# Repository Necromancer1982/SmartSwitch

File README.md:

# SmartSwitch
## Flush-mounted Module to control shutters / realize an intermediate switch with ESP8266

**Version History**

- SmartSwitch V1.2  04/2018   1st official public Version
- SmartSwitch V1.3  05/2018   ADD: Additional Fuse (F2, 4A) for consumer current
- **Software now avaliable for ArduinoIDE (including OTA)**

**Vision**

During the construction of our new house, we’ve decided to install motorized roller shutters. To control them, we first used only standard shutter-push-buttons, right beside the correspondent window. As second step a *smart solution* should be established.

Inspired by Leo-Andres Hofmann’s “230V I/O Modul für ESP8266” ([LUANI](https://luani.de/projekte/esp8266-hvio/)), I’ve decided to develop my own module to sense the shutter-push-buttons and control the motorization.
By its dimensions, the module perfectly fits into a standard round In-Wall-Pattress (inner diameter: 60mm). If its a so called "deep" pattress, the shutter-push-buttons can also be installed on top of the module and there is enough space left for wires and terminals.

Basis of the module is a ESP-12F, an integrated WLAN-Module which controls two changeover relays to move the shutters. 

The operation of the module can either be controlled by the already existing push-buttons, or via MQTT-Messages by WLAN, central controlled via [OpenHab2](https://docs.openhab.org/index.html), running on my Raspberry Pi Zero W. Therefore, a movement of the shutters regarding time or special events, for example time of dusk and down ([Astro Bindings](https://docs.openhab.org/addons/bindings/astro/readme.html)) can be realized. Also an automatized shadowing regarding sun position, global radiation and inside / outside temperature will be possible.

**Hardware**

Beside the WLAN-Module and the relays (contact rating 1500VA, 6A/250V), a power supply consisting of a AC/DC-Converter HI-Link HLK-PM01 (5V/600mA) to serve the relays and a voltage regulator TS1117 (LowDrop 3V) to serve the remaining circuit, a 2-chanel power sense circuit to detect 230V levels for the controller and interfaces like UART, I²C and analog/digital IO are included on the board. A push button for hardware reset is also implemented on bottom side of the PCB.

Three soldering jumpers give the opportunity to decide if the relays should act as an intermediate switch to implement the module in an already existing light-installation or to act as a roller-shutter-controlling device. Therefore, the first relay powers the motor during the second relay controls moving direction. Via a fourth soldering Jumper it is possible to supply mains voltage to the relays, so for roller shutter function, there is no need to connect phase two times, for supplying the module and supplying the motor. 

The power supply of the module is secured by a SMD-Fuse (500mA) and a varistor (275V) against overload.

**Software**

In addition to the firmware ([NodeMCU](https://nodemcu.readthedocs.io/en/master/)) there are mainly four LUA-Scripts on the Module.

The Init-File tries to connect to the access point whose SSID and password is stored at the ESP. If the connection couldn’t be established, the ESP himself opens an access point and starts an end user setup to give the user the possibility to enter SSID and password of an already existing access point (Router).

If the connection is established, two more software modules will be started. The MQTT-Module starts to configure the implemented MQTT-Client, opens a connection to the MQTT-Broker which is defined (IP, Port) in the MQTT.ini file and provides several procedures for MQTT communication. The INI-Handling-Module provides two more procedures for easy INI-File access by using “Key” and “Value” data.

Finally, the main program will be started.

:+1: _UPDATE_

Now I'd also written a new software for ArduinoIDE.
The main advantage of this new sketch is the possibility of updating the software via OTA (Over the Air update via WiFi).
After flashing the sketch via serial adapter for the first time, the module can be found and flashed via ArduinoIDE OTA-Functionality.

Additionally there are a few smaller upgrades and BugFixes implemented in the new software.

The functionality of the Arduino-Software is mostly the same as the LUA-Skript.
The module tries to connect to the last stored access point. If no connection could be established the module starts its implemented enduser setup. SSID and password of the AP and also the site of usage and MQTT-borker IP can be configured. After this initialisation the module starts its normal operation and can be either controlled via the already existing push buttons or MQTT-Commands.

**Function**

During normal operation, the main program offers the opportunity to control the module via the shutter-push-buttons by using both of the power sense inputs. (Only LUA-Skript: If both buttons were pushed synchronously the module changes to teaching mode.) Via MQTT-Command "TEACH", the module changes to teaching mode. Because of the fact that simple shutter motors neither feedback their position nor the state of their limit switches, the position of the shutter can only be traced by the time, the motor is in motion. Therefore, in teaching mode, the time to reach both final positions can be stored in module by closing and reopening the shutter completely.
After that, a short push of a button results in moving to respective end position. If the button will be pressed longer then 1s the shutter moves as long as the button is pressed or final position is reached. By releasing the button, the current position of the shutter will be calculated regarding the time, the motor was in motion and will be stored in the module. Thus offers the opportunity to start motion from any position of the shutter or moving the shutter to a particular position (e.g. closing until only shutter slots are open).

But not only manual operation by pushing a button is possible. As mentioned, the module acts also as a MQTT-Client. Via messages to the MQTT-Topic (LUA-Skript: which is also settled in MQTT.ini file; ARDUINO-Skript: /SmartSwitch/SmartSwitch_\<SITE or MAC\>/), motion to the final position is possible, either by command “UP” or “DOWN”. By sending a value from 0 to 100 the shutter moves to the correspondent position in percent. If the desired position is reached or the shutter reaches end position, the current position will be also send as MQTT-Message to the broker (ARDUINO: Also the RSSI of the module will be sent). Therefore, a visualization of the current position e.g. with  [HabPanel von OpenHab](https://docs.openhab.org/addons/uis/habpanel/readme.html) is possible.

**Safety**

By operating the module at mains voltage, the active parts and pins should be covered against directly and indirectly touching. Therefore, I’ve designed a Bottom-Coverage ([Project at Thingiverse](https://www.thingiverse.com/thing:3085953)) for the module with FreeCAD and printed it with my Anet A6 3D-Printer. As positive side effect of the coverage, all SMT-Components on bottom side are protected against mechanical damages.

### Safety Disclaimer

Building and usage at your own risk. SmartSwitch uses potentially lethal mains voltages.

If you are a beginner in electronics or don't have the proper experience to work with mains voltage, consult a professional! I am not liable for any mishaps that may occur due to misuse of SmartSwitch or electrical system (including mains power) including but not limited to: errors or omissions, loss of life, or property damage. Take all safety precautions as necessary. You are fully responsible for your actions, perform them at your own risk!

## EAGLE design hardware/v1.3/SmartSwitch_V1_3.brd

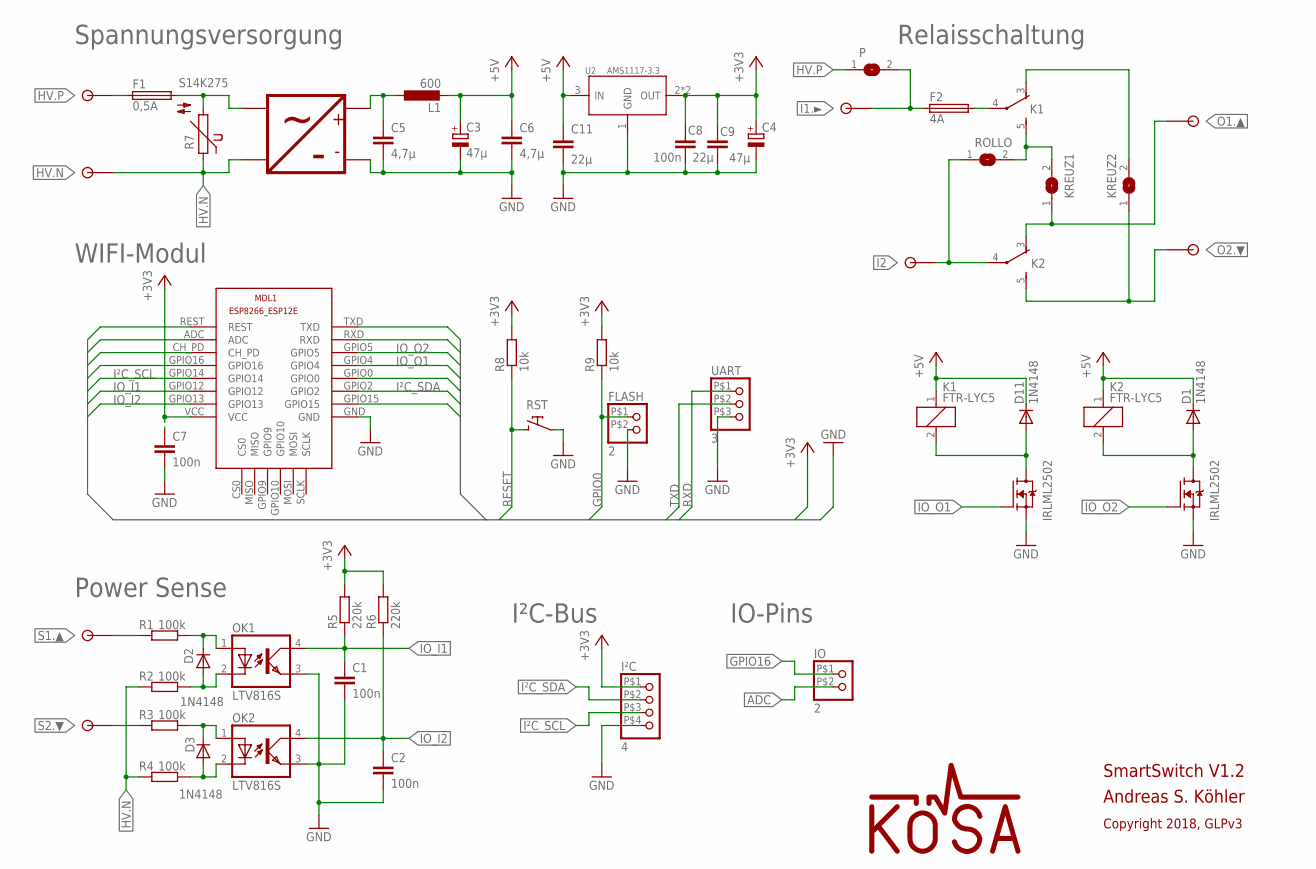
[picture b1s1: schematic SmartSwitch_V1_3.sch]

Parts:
C1, C2, C7, C8: 100n; C0805
C3, C4: 47µ; E2-5
C5, C6: 4,7µ; C0805
C9, C11: 22µ; C0805
D1, D2, D3, D11: 1N4148; SOD323-W
F1: 0,5A; SMD_FUSE_HOLDER
F2: 4A; SMD_FUSE_HOLDER
FLASH: 2; 1X02_SMALL
IO: 2; 1X02_SMALL
I²C: 4; 1X04_SMALL
K1, K2: FTR-LYC5; FTR-LYC
KREUZ1, KREUZ2: SJW
L1: 600; L3225P
MDL1: 1; ESP8266-ESP12E
OK1, OK2: LTV816S; SMD4
P: SJW
R1, R2, R3, R4: 100k; R1206
R5, R6: 220k; R1206
R7: S14K275; S14K275_
R8, R9: 10k; R1206
ROLLO: SJW
RST: SMD-TASTER_REICHELT_KMR_231_G_LFS
U2: AMS1117-3.3; SOT-223
U$1: HLK-PM01
U$2, U$3, U$4, U$5: RND_205-00276; RND205-00276
U$7, U$8: IRLML2502; SOT23
UART: 3; 1X03_SMALL

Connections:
+3V3: C4.+, C7.1, C8.1, C9.1, I²C.P$1 (1), MDL1.CH_PD, MDL1.VCC, R5.2, R6.2, R8.2, R9.2, U2.2 (OUT), U2.TER (OUT)
+5V: C3.+, C6.1, C11.1, D1.C, D11.C, K1.1, K2.1, L1.2, U2.3 (IN)
ADC: IO.P$2 (2), MDL1.ADC
GND: C1.2, C2.2, C3.-, C4.-, C5.2, C6.2, C7.2, C8.2, C9.2, C11.2, FLASH.P$2 (2), I²C.P$4 (4), MDL1.GND, MDL1.GPIO15, OK1.3 (EMIT), OK2.3 (EMIT), RST.1_1 (A), RST.1_2 (A), U2.1 (GND), U$1.DC-, U$7.2 (S), U$8.2 (S), UART.P$3 (3)
GPIO0: FLASH.P$1 (1), MDL1.GPIO0, R9.1
GPIO16: IO.P$1 (1), MDL1.GPIO16
HV.N: R2.1, R4.1, R7.1, U$1.AC2, U$2.P$2
HV.P: F1.P$1 (1), P.1, U$2.P$1
I1.►: F2.P$1 (1), P.2, U$4.P$1
I2: K2.4, ROLLO.1, U$3.P$1
IO_I1: C1.1, MDL1.GPIO12, OK1.4 (COL), R5.1
IO_I2: C2.1, MDL1.GPIO13, OK2.4 (COL), R6.1
IO_O1: MDL1.GPIO4, U$7.1 (G)
IO_O2: MDL1.GPIO5, U$8.1 (G)
I²C_SCL: I²C.P$3 (3), MDL1.GPIO14
I²C_SDA: I²C.P$2 (2), MDL1.GPIO2
unnamed: F2.P$2 (2), K1.4
unnamed: K1.5 (S), KREUZ1.2, ROLLO.2
unnamed: K1.3 (O), KREUZ2.2
unnamed: C5.1, L1.1, U$1.DC+
unnamed: F1.P$2 (2), R7.2, U$1.AC1
unnamed: D2.C, OK1.1 (A), R1.2
unnamed: D3.C, OK2.1 (A), R3.2
unnamed: D2.A, OK1.2 (C), R2.2
unnamed: D3.A, OK2.2 (C), R4.2
unnamed: D11.A, K1.2, U$7.3 (D)
unnamed: D1.A, K2.2, U$8.3 (D)
O1.▲: K2.3 (O), KREUZ1.1, U$3.P$2
O2.▼: K2.5 (S), KREUZ2.1, U$4.P$2
RESET: MDL1.REST, R8.1, RST.2_1 (B), RST.2_2 (B)
RXD: MDL1.RXD, UART.P$1 (1)
S1.▲: R1.1, U$5.P$2
S2.▼: R3.1, U$5.P$1
TXD: MDL1.TXD, UART.P$2 (2)

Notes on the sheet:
Spannungsversorgung
Power Sense
Relaisschaltung
WIFI-Modul
I²C-Bus
IO-Pins
SmartSwitch V1.2
Andreas S. Köhler
Copyright 2018, GLPv3

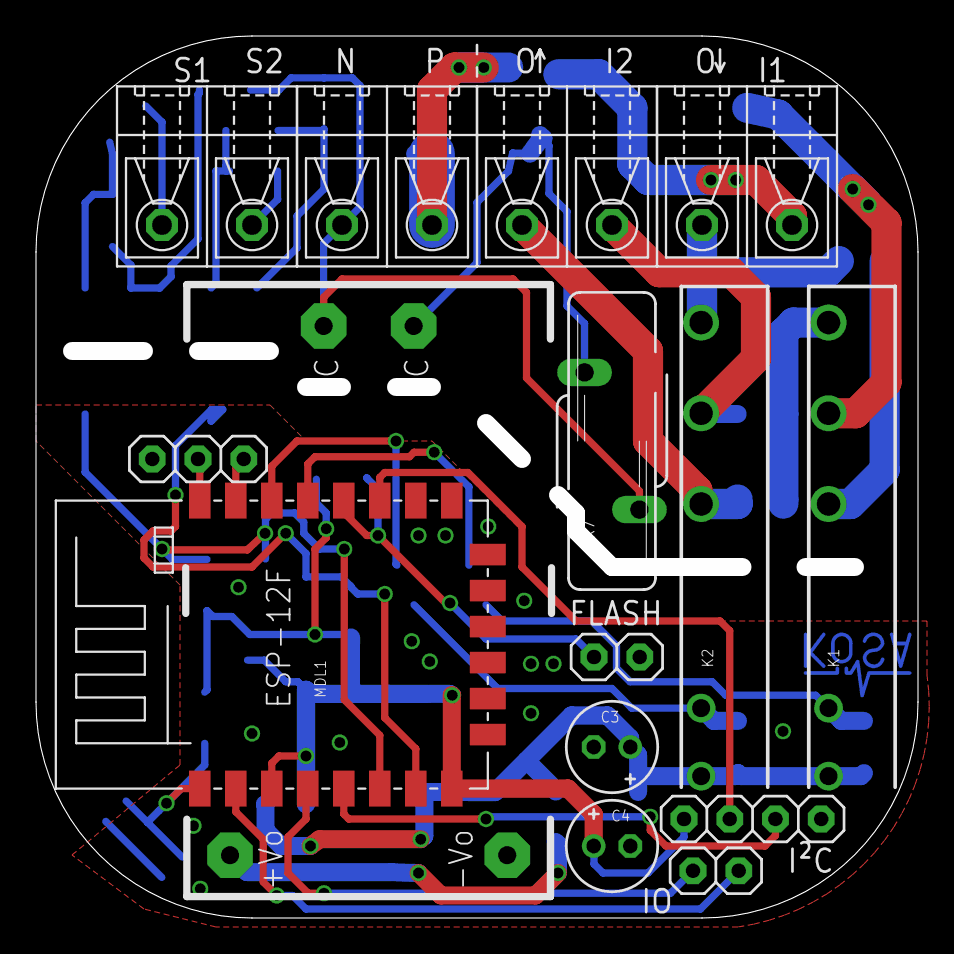
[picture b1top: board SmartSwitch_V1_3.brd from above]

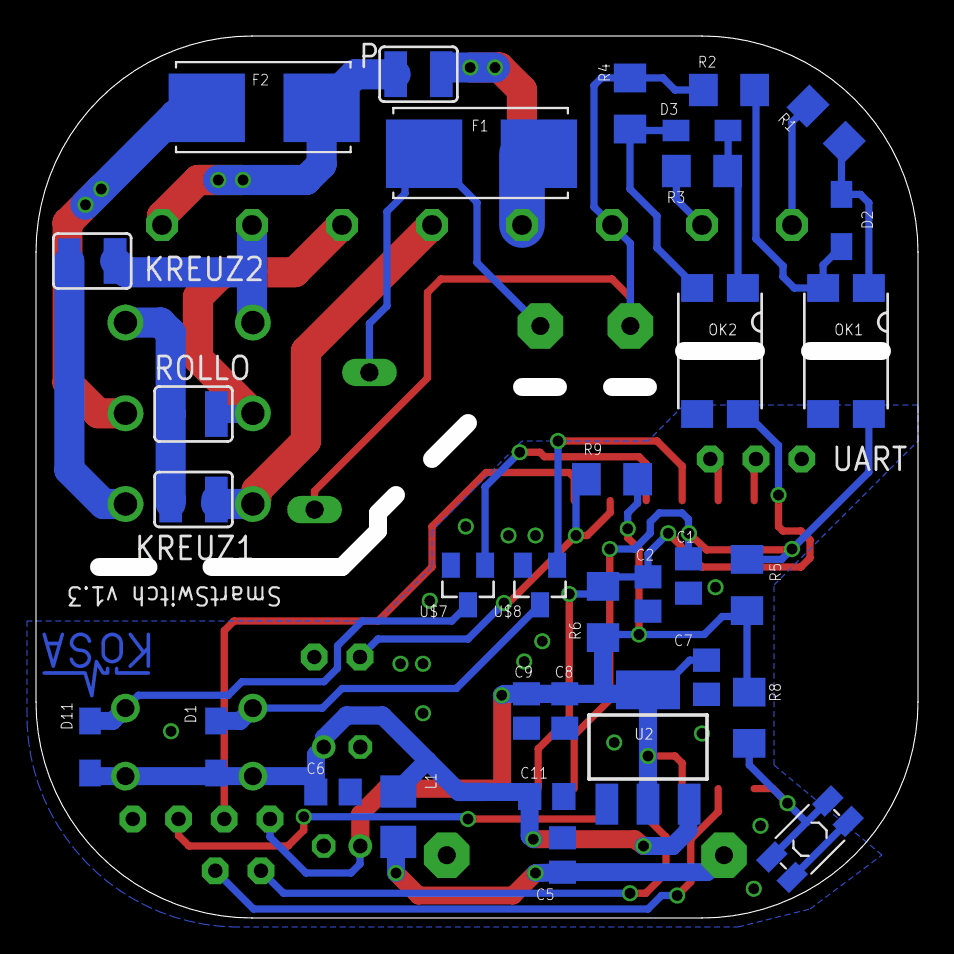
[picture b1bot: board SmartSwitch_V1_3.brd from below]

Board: 2 copper layers, 48.0 x 48.0 mm, 48 parts (33 on the bottom side), 34 nets.

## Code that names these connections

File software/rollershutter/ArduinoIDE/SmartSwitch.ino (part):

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unsigned long interval = 1000;                                                        // Variable to store interval of MQTT-Connection-Check    *** Interval of MQTT-Check   ***
String ProgRevision = "SmartSwitch V1.2";                                             // Variable to store Software-Revision                    *** Software-Revision        ***
// *** Needed IOs ***************************************************************************************************************************************************************
#define IO_I1 12                                                                      // Map IO_I1 (Input: UP) to GPIO12
#define IO_I2 13                                                                      // Map IO_I2 (Input: DOWN) to GPIO13
#define IO_O1 4                                                                       // Map IO_O1 (Relais: DIRECTION) to GPIO4
#define IO_O2 5                                                                       // Map IO_O2 (Relais: POWER) to GPIO5
// *** Needed Services **********************************************************************************************************************************************************
WiFiClient espClient;                                                                 // Create a WiFi-Client
PubSubClient client(espClient);                                                       // Create a PubSubClient-Object (MQTT)
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// ##############################################################################################################################################################################
void setup() {
// *** Initialize IO-Pins *******************************************************************************************************************************************************
  pinMode(IO_I1, INPUT);                                                              // Set IO_I1 as Input-Pin
  pinMode(IO_I2, INPUT);                                                              // Set IO_I2 as Input-Pin
  pinMode(IO_O1, OUTPUT);                                                             // Set IO_O1 as Output-Pin
  pinMode(IO_O2, OUTPUT);                                                             // Set IO_O2 as Output-Pin
  digitalWrite(IO_O1, LOW);                                                           // Set IO_O1 LOW
  digitalWrite(IO_O2, LOW);                                                           // Set IO_O2 LOW
// *** Read initial values from EEPROM ******************************************************************************************************************************************  
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
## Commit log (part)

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2018-04-09 1 upload
2018-04-09 test
2018-04-10 Rename SmartSwitch.brd to SmartSwitch_V1_1.brd
2018-04-13 Translate ReadMe.md to english
2018-04-17 Create LICENSE
2018-08-17 BugFix
    BugFix to guarantee complete opening or closing with UP/DOWN command.
    Opening / Closing will last 3s longer than actual teached time.
2018-09-04 added Reichelt part url link
2018-09-26 Equalization of BOM and Schematic
    Mixup of "my" standard driver transistor (IRLML2502, 20V 4,2A) and the used one (IRLML2402, 20V, 1,2A) was adjusted.
    Both will work in the given circuit becaus only a coil-current of 35mA is necessary.
2019-01-30 Create t
2019-01-30 Software now avaliable for ArduinoIDE
    Additional software for ArduinoIDE avaliable:
    - Extended Endusersetup (including Site- and MQTT-Configuration)
    - OTA-Update possible
2019-01-31 BugFix
    - Operation via Push-Buttons should also be possible if MQTT-Connection is broken
    - Reasonable displaying of "site" and "broker" in WiFiManager during first initialisation
2019-01-31 ADD: Instructionset for Arduino-Sketch
2019-02-03 BugFix (If EEPROM-Content isn't a number...)
    After first initialisazion and bootup of the module, the EEPROM-Content isn't defined.
    Because of the fact that the content will be read, the Software gets a "nan" error.
    Now there is a errorhandling if one of the variables in EEPROM isn't a number.
2019-03-04 BugFix - Retaining position, extended status messages
2020-04-20 Update SmartSwitch.ino
    corrected WiFiMangager Parameter
2020-04-20 Update SmartSwitch.ino
    change switch of relais in moition stop
2020-04-20 Update SmartSwitch.ino
    delete send command in stop motion- makes no sense for me
2020-04-20 Update SmartSwitch.ino
    correct pos from int to float 0.0f and 100.0f

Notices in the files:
software/rollershutter/ArduinoIDE/SmartSwitch.ino:
Copyright © 2019, Andreas S. Köhler
This program is free software: you can redistribute it and/or modify
it under the terms of the GNU General Public License as published by
the Free Software Foundation, either version 3 of the License, or
(at your option) any later version.
